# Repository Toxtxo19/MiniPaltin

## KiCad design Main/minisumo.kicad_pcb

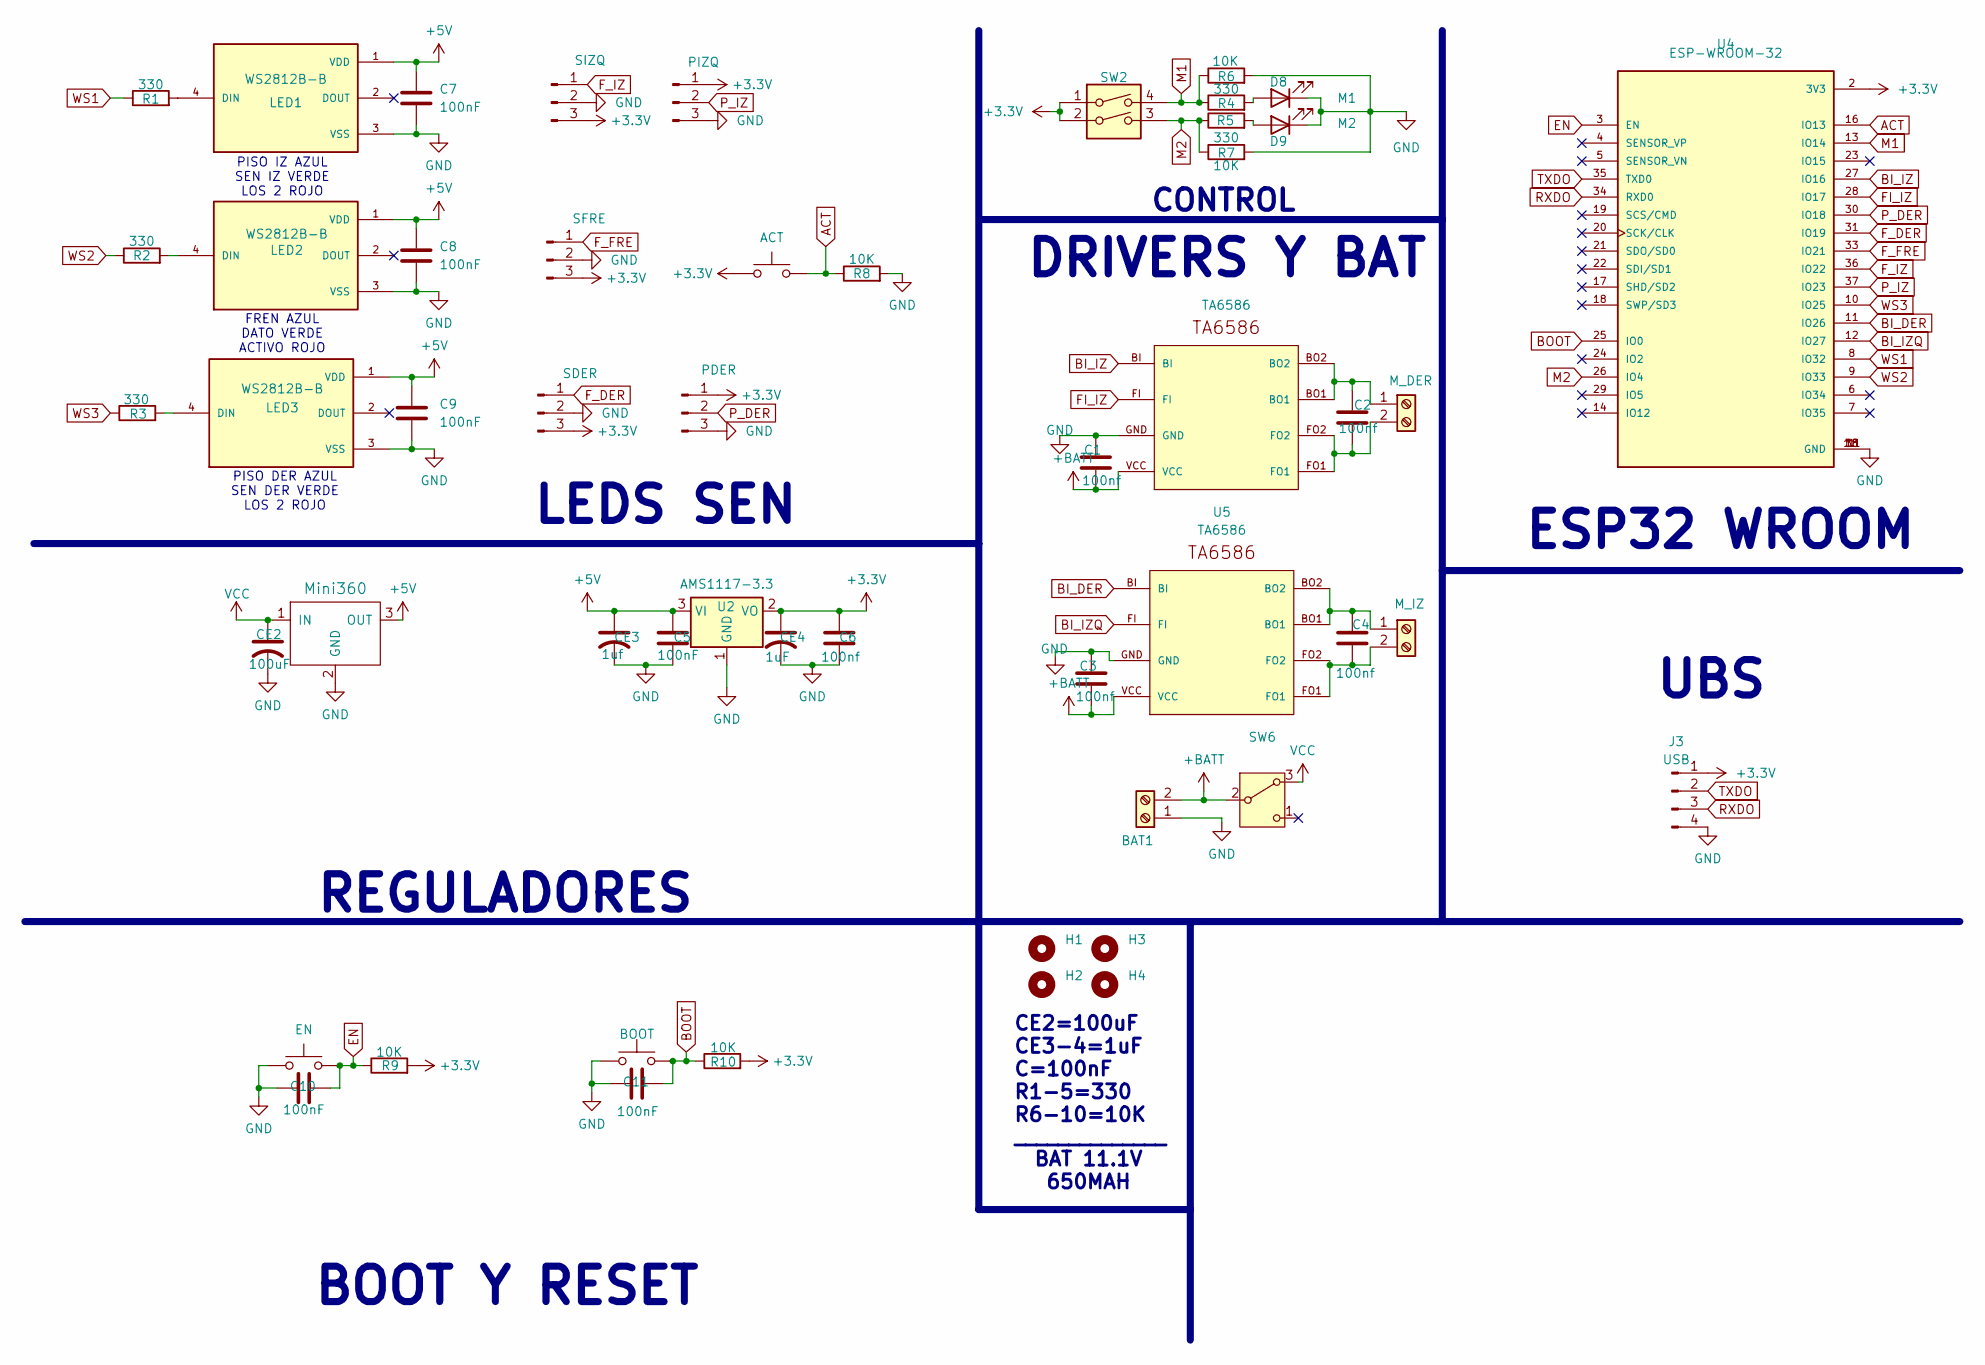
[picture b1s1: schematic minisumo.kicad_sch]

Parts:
BAT1: Screw_Terminal_01x02; AMASS_XT30U-F_1x02_P5.0mm_Vertical
C1, C2, C3, C4, C6: 100nf; C_0805_2012Metric_Pad1.18x1.45mm_HandSolder
C5, C7, C8, C9, C10, C11: 100nF; C_0805_2012Metric_Pad1.18x1.45mm_HandSolder
CE2: 100uF; CP_EIA-7343-20_Kemet-V_HandSolder
CE3: 1uf; C_0805_2012Metric_Pad1.18x1.45mm_HandSolder
CE4: 1uF; C_0805_2012Metric_Pad1.18x1.45mm_HandSolder
D8: M1; LED_0805_2012Metric_Pad1.15x1.40mm_HandSolder
D9: M2; LED_0805_2012Metric_Pad1.15x1.40mm_HandSolder
H1, H2, H3, H4: MountingHole; MountingHole_2.2mm_M2_ISO7380
J2: M_DER; JST_XH_B2B-XH-A_1x02_P2.50mm_Vertical
J3: USB; PinHeader_1x04_P2.54mm_Vertical
J4: M_IZ; JST_XH_B2B-XH-A_1x02_P2.50mm_Vertical
J7: SIZQ; JST_XH_B3B-XH-A_1x03_P2.50mm_Vertical
J8: SFRE; JST_XH_B3B-XH-A_1x03_P2.50mm_Vertical
J9: PIZQ; JST_XH_B3B-XH-A_1x03_P2.50mm_Vertical
J10: SDER; JST_XH_B3B-XH-A_1x03_P2.50mm_Vertical
J11: PDER; JST_XH_B3B-XH-A_1x03_P2.50mm_Vertical
LED1, LED2, LED3: WS2812B-B; LED_WS2812B_PLCC4_5.0x5.0mm_P3.2mm; PARTREV 5
R1, R2, R3, R4, R5: 330; R_0805_2012Metric_Pad1.20x1.40mm_HandSolder
R6, R7, R8, R9, R10: 10K; R_0805_2012Metric_Pad1.20x1.40mm_HandSolder
SW1: ACT; SW_SPST_CK_RS282G05A3
SW2: SW_DIP_x02; SW_DIP_SPSTx02_Slide_6.7x6.64mm_W8.61mm_P2.54mm_LowProfile
SW3: EN; SW_SPST_CK_RS282G05A3
SW4: BOOT; SW_SPST_CK_RS282G05A3
SW6: SW_Nidec_CAS-120A1; SW_Slide-03_P2.54_L9_W4_H7
U2: AMS1117-3.3; SOT-223-3_TabPin2
U3, U5: TA6586; TA6586-FOOTPRINT
U4: ESP-WROOM-32; MODULE_ESP-WROOM-32
U6: Mini360; Mini360_step-down

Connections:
+3.3V: C6.1, CE4.1, J3.1, J7.3, J8.3, J9.1, J10.3, J11.1, R9.2, R10.2, SW1.1, SW2.1, SW2.2, U2.2 (VO), U4.2 (3V3)
+5V: C5.1, C7.1, C8.1, C9.1, CE3.1, LED1.1 (VDD), LED2.1 (VDD), LED3.1 (VDD), U2.3 (VI), U6.3 (OUT)
+BATT: BAT1.2, C1.2, C3.2, SW6.2 (B), U3.VCC, U5.VCC
ACT: R8.1, SW1.2, U4.16 (IO13)
BI_DER: U4.11 (IO26), U5.BI
BI_IZ: U3.BI, U4.27 (IO16)
BI_IZQ: U4.12 (IO27), U5.FI
BOOT: C11.1, R10.1, SW4.2, U4.25 (IO0)
EN: C10.1, R9.1, SW3.2, U4.3 (EN)
FI_IZ: U3.FI, U4.28 (IO17)
F_DER: J10.1, U4.31 (IO19)
F_FRE: J8.1, U4.33 (IO21)
F_IZ: J7.1, U4.36 (IO22)
GND: BAT1.1, C1.1, C3.1, C5.2, C6.2, C7.2, C8.2, C9.2, C10.2, C11.2, CE2.2, CE3.2, CE4.2, D8.1 (K), D9.1 (K), J3.4, J7.2, J8.2, J9.3, J10.2, J11.3, LED1.3 (VSS), LED2.3 (VSS), LED3.3 (VSS), R6.2, R7.2, R8.2, SW3.1, SW4.1, U2.1 (GND), U3.GND, U4.1 (GND), U4.1.1 (GND), U4.15 (GND), U4.38 (GND), U5.GND, U6.2 (GND)
M1: R4.1, R6.1, SW2.4, U4.13 (IO14)
M2: R5.1, R7.1, SW2.3, U4.26 (IO4)
unnamed: D8.2 (A), R4.2
unnamed: D9.2 (A), R5.2
unnamed: C2.1, J2.1, U3.BO1, U3.BO2
unnamed: C2.2, J2.2, U3.FO1, U3.FO2
unnamed: C4.1, J4.1, U5.BO1, U5.BO2
unnamed: C4.2, J4.2, U5.FO1, U5.FO2
unnamed: LED1.4 (DIN), R1.2
unnamed: LED2.4 (DIN), R2.2
unnamed: LED3.4 (DIN), R3.2
P_DER: J11.2, U4.30 (IO18)
P_IZ: J9.2, U4.37 (IO23)
RXDO: J3.3, U4.34 (RXD0)
TXDO: J3.2, U4.35 (TXD0)
VCC: CE2.1, SW6.3 (A), U6.1 (IN)
WS1: R1.1, U4.8 (IO32)
WS2: R2.1, U4.9 (IO33)
WS3: R3.1, U4.10 (IO25)

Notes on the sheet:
PISO DER AZUL SEN DER VERDE LOS 2 ROJO
DRIVERS Y BAT
FREN AZUL DATO VERDE ACTIVO ROJO
BOOT Y RESET
CE2=100uF CE3-4=1uF C=100nF R1-5=330 R6-10=10K ______________
CONTROL
LEDS SEN
UBS
REGULADORES
BAT 11.1V 650MAH
ESP32 WROOM
PISO IZ AZUL SEN IZ VERDE LOS 2 ROJO

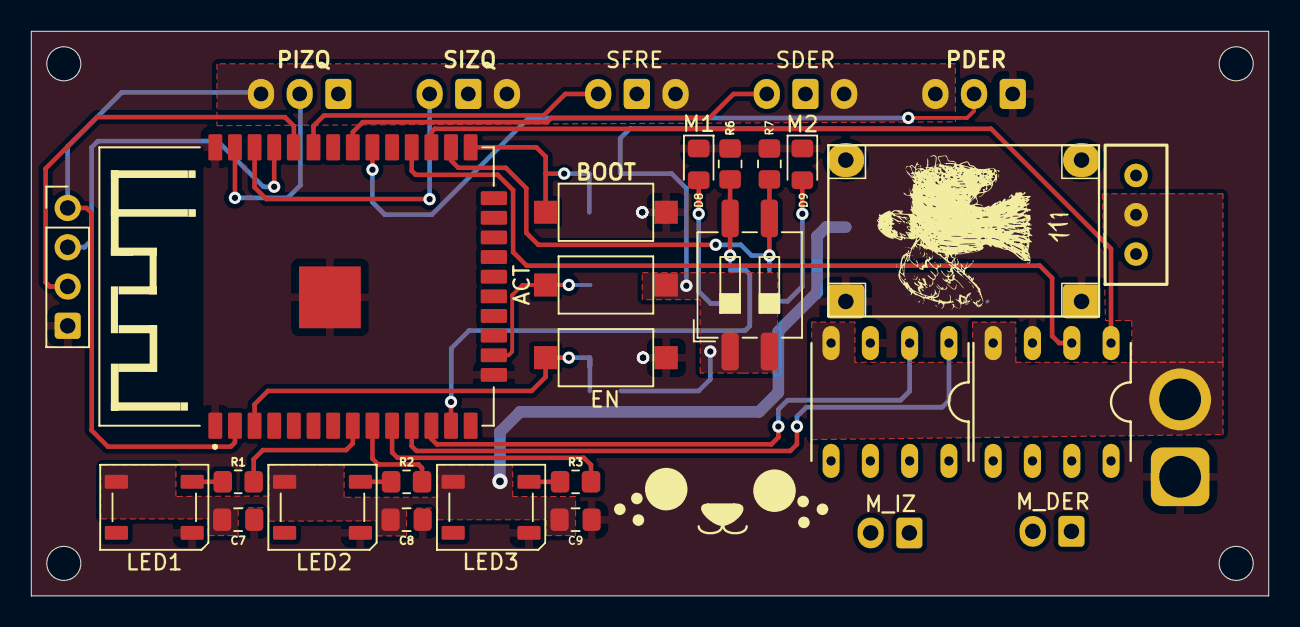
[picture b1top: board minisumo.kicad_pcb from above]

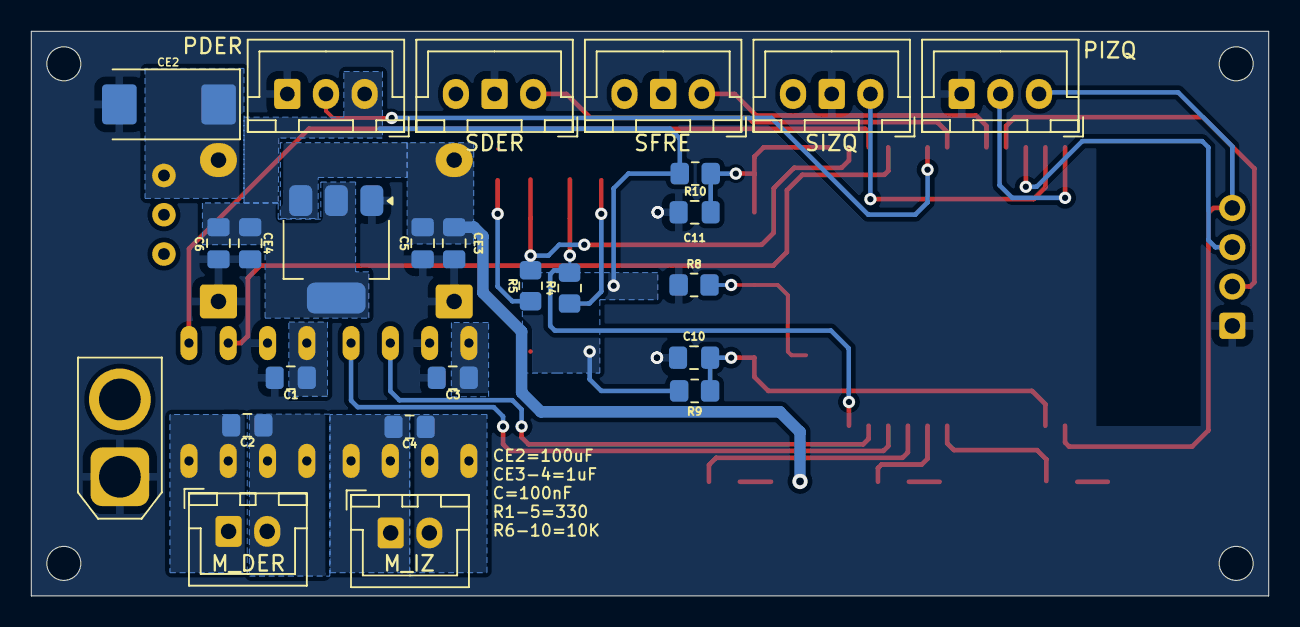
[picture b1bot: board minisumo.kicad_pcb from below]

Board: 4 copper layers, 80.0 x 36.5 mm, 52 parts (25 on the bottom side), 33 nets.

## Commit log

2025-10-07 el super maquiabelico paltin
2025-10-09 actualizado
2025-10-09 actual:)
2025-10-09 actual
2025-10-10 vaquin
2025-10-11 fack
